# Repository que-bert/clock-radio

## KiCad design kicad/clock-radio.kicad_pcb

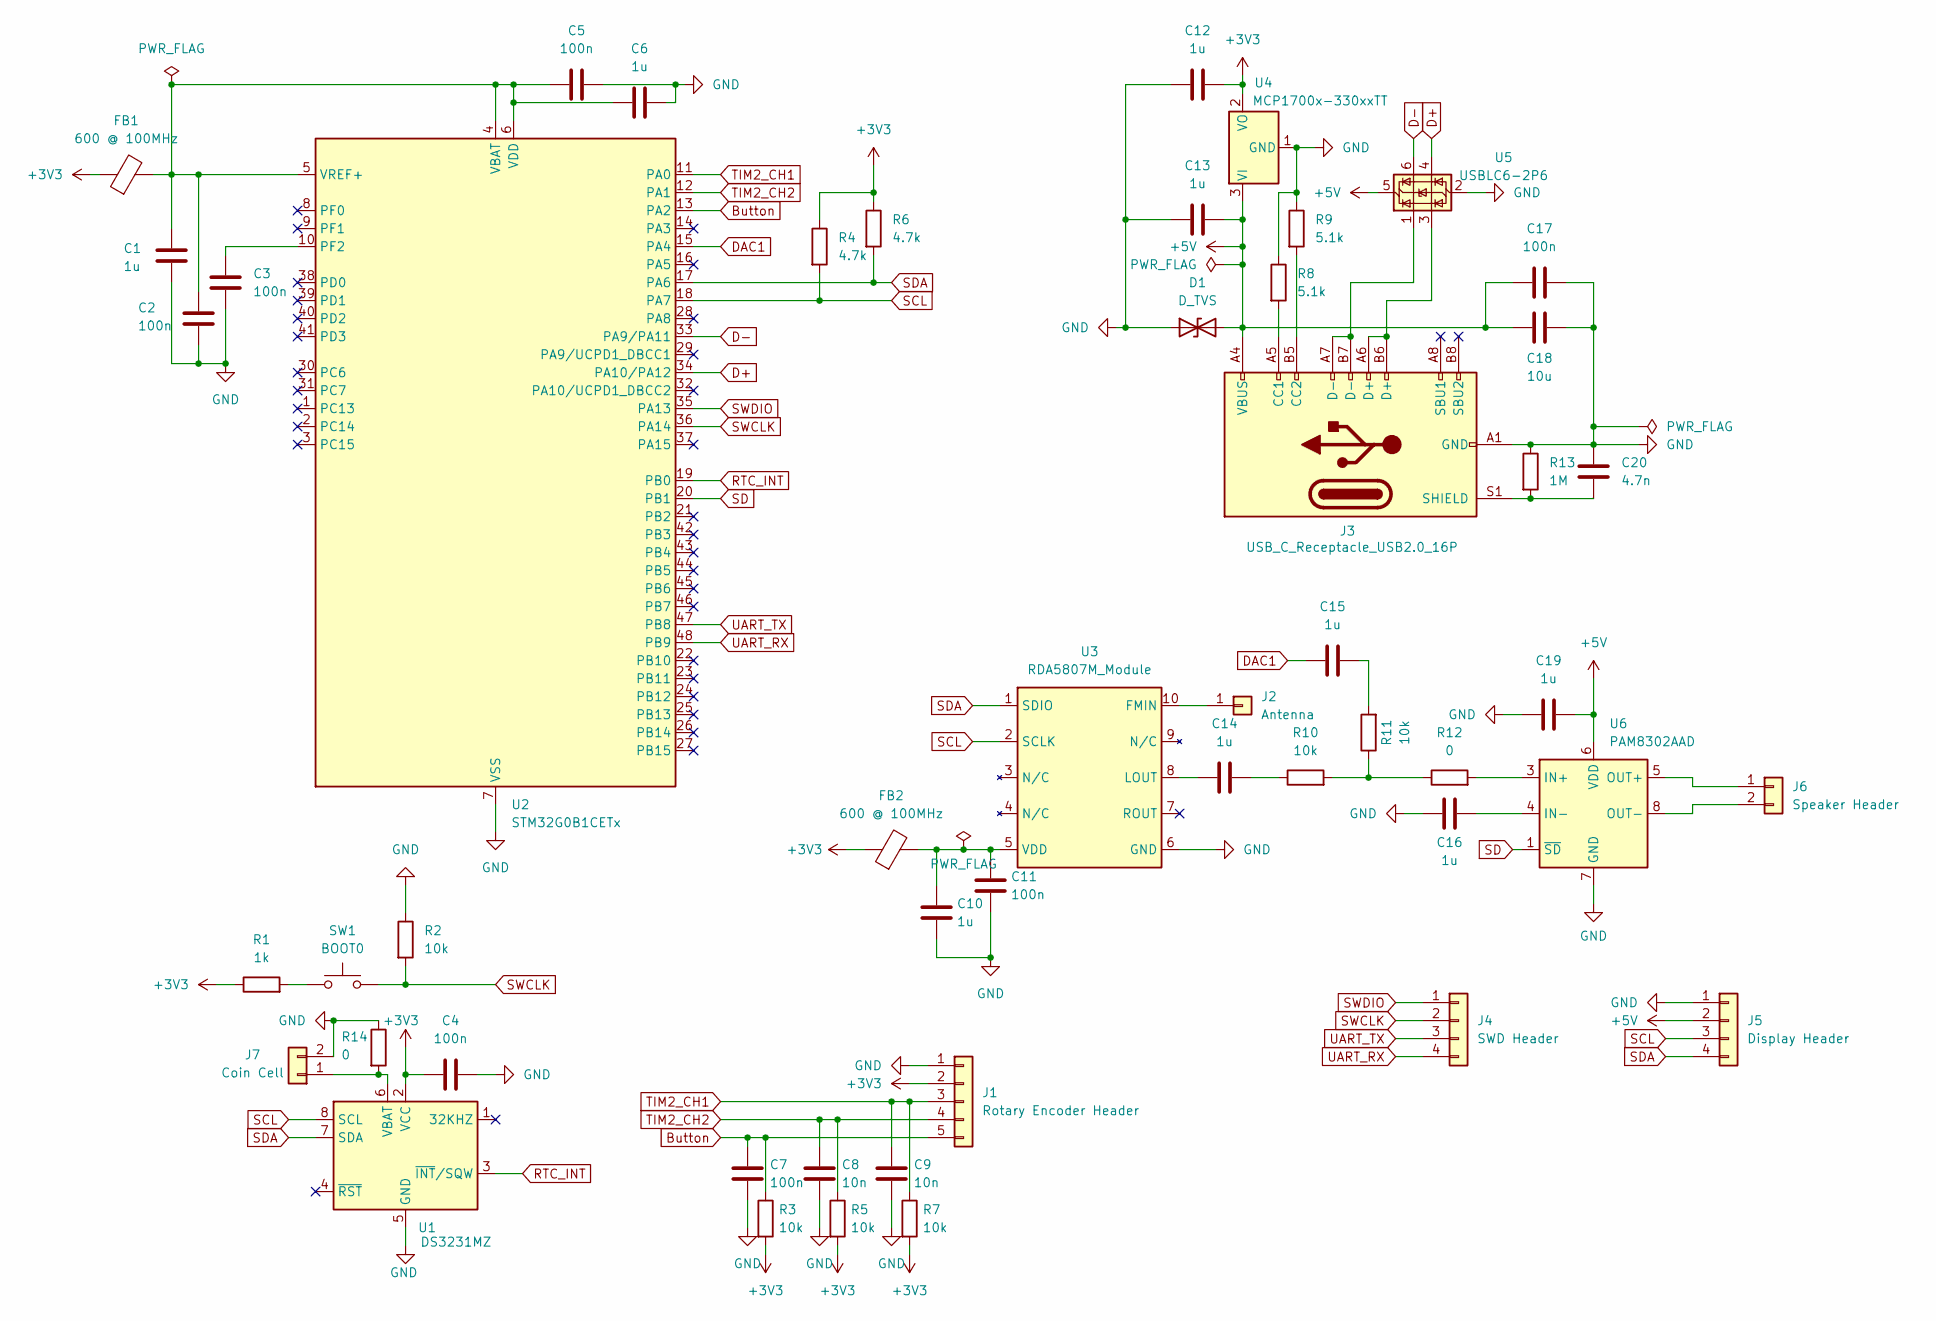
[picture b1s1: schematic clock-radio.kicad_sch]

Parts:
C1, C6, C10, C12, C13, C14, C15, C16, C19: 1u; C_0402_1005Metric_Pad0.74x0.62mm_HandSolder
C2, C3, C4, C5, C7, C11, C17: 100n; C_0402_1005Metric_Pad0.74x0.62mm_HandSolder
C8, C9: 10n; C_0402_1005Metric_Pad0.74x0.62mm_HandSolder
C18: 10u; C_0402_1005Metric_Pad0.74x0.62mm_HandSolder
C20: 4.7n; C_0402_1005Metric_Pad0.74x0.62mm_HandSolder
D1: D_TVS; D_SMA-SMB_Universal_Handsoldering
FB1, FB2: 600 @ 100MHz; C_0603_1608Metric_Pad1.08x0.95mm_HandSolder
J1: Rotary Encoder Header; PinSocket_1x05_P2.54mm_Vertical
J2: Antenna; SolderWire-0.75sqmm_1x01_D1.25mm_OD2.3mm
J3: USB_C_Receptacle_USB2.0_16P; USB_C_Receptacle_HCTL_HC-TYPE-C-16P-01A
J4: SWD Header; PinSocket_1x04_P2.54mm_Vertical
J5: Display Header; PinSocket_1x04_P2.54mm_Vertical
J6: Speaker Header; PinSocket_1x02_P2.54mm_Vertical
J7: Coin Cell; PinSocket_1x02_P2.54mm_Vertical
R1: 1k; R_0402_1005Metric_Pad0.72x0.64mm_HandSolder
R2, R3, R5, R7, R10, R11: 10k; R_0402_1005Metric_Pad0.72x0.64mm_HandSolder
R4, R6: 4.7k; R_0402_1005Metric_Pad0.72x0.64mm_HandSolder
R8, R9: 5.1k; R_0402_1005Metric_Pad0.72x0.64mm_HandSolder
R12, R14: 0; R_0402_1005Metric_Pad0.72x0.64mm_HandSolder
R13: 1M; R_0402_1005Metric_Pad0.72x0.64mm_HandSolder
SW1: BOOT0; SW_SPST_B3U-1000P
U1: DS3231MZ; SOIC-8_3.9x4.9mm_P1.27mm
U2: STM32G0B1CETx; LQFP-48_7x7mm_P0.5mm
U3: RDA5807M_Module; RDA5807M_Module_SM
U4: MCP1700x-330xxTT; SOT-23
U5: USBLC6-2P6; SOT-666
U6: PAM8302AAD; MSOP-8_3x3mm_P0.65mm

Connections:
+3V3: C4.1, C12.2, FB1.1, FB2.1, J1.2, R1.1, R3.2, R4.1, R5.2, R6.1, R7.2, U1.2 (VCC), U4.2 (VO); also elsewhere on the board
+5V: C13.2, C17.1, C18.1, C19.2, D1.2 (A2), J3.A4 (VBUS), J3.A9 (VBUS), J3.B4 (VBUS), J3.B9 (VBUS), J5.2, U4.3 (VI), U5.5 (VBUS), U6.6 (VDD)
Button: C7.1, J1.5, R3.1, U2.13 (PA2)
D+: U2.34 (PA10/PA12), U5.4 (I/O2)
D-: U2.33 (PA9/PA11), U5.6 (I/O1)
DAC1: C15.1, U2.15 (PA4)
GND: C1.1, C2.1, C3.1, C4.2, C5.2, C6.2, C7.2, C8.2, C9.2, C10.2, C11.2, C12.1, C13.1, C16.2, C17.2, C18.2, C19.1, C20.1, D1.1 (A1), J1.1, J3.A1 (GND), J3.A12 (GND), J3.B1 (GND), J3.B12 (GND), J5.1, J7.2, R2.1, R8.1, R9.1, R13.1, R14.1, U1.5 (GND), U2.7 (VSS), U3.6 (GND), U4.1 (GND), U5.2 (GND), U6.7 (GND); also elsewhere on the board
unnamed: C14.2, R10.1
unnamed: C15.2, R11.2
unnamed: J2.1, U3.10 (FMIN)
unnamed: J3.A5 (CC1), R8.2
unnamed: J3.B5 (CC2), R9.2
unnamed: J3.A6 (D+), J3.B6 (D+), U5.3 (I/O2)
unnamed: J3.A7 (D-), J3.B7 (D-), U5.1 (I/O1)
unnamed: C20.2, J3.S1 (SHIELD), R13.2
unnamed: J6.1, U6.5 (OUT+)
unnamed: J6.2, U6.8 (OUT-)
unnamed: J7.1, R14.2, U1.6 (VBAT)
unnamed: R1.2, SW1.1
unnamed: R10.2, R11.1, R12.1
unnamed: C3.2, U2.10 (PF2)
unnamed: C1.2, C2.2, C5.1, C6.1, FB1.2, U2.4 (VBAT), U2.5 (VREF+), U2.6 (VDD)
unnamed: C14.1, U3.8 (LOUT)
unnamed: C10.1, C11.1, FB2.2, U3.5 (VDD)
unnamed: R12.2, U6.3 (IN+)
unnamed: C16.1, U6.4 (IN-)
RTC_INT: U1.3 (~INT/SQW), U2.19 (PB0)
SCL: J5.3, R4.2, U1.8 (SCL), U2.18 (PA7), U3.2 (SCLK)
SD: U2.20 (PB1), U6.1 (~SD)
SDA: J5.4, R6.2, U1.7 (SDA), U2.17 (PA6), U3.1 (SDIO)
SWCLK: J4.2, R2.2, SW1.2, U2.36 (PA14)
SWDIO: J4.1, U2.35 (PA13)
TIM2_CH1: C9.1, J1.3, R7.1, U2.11 (PA0)
TIM2_CH2: C8.1, J1.4, R5.1, U2.12 (PA1)
UART_RX: J4.4, U2.48 (PB9)
UART_TX: J4.3, U2.47 (PB8)

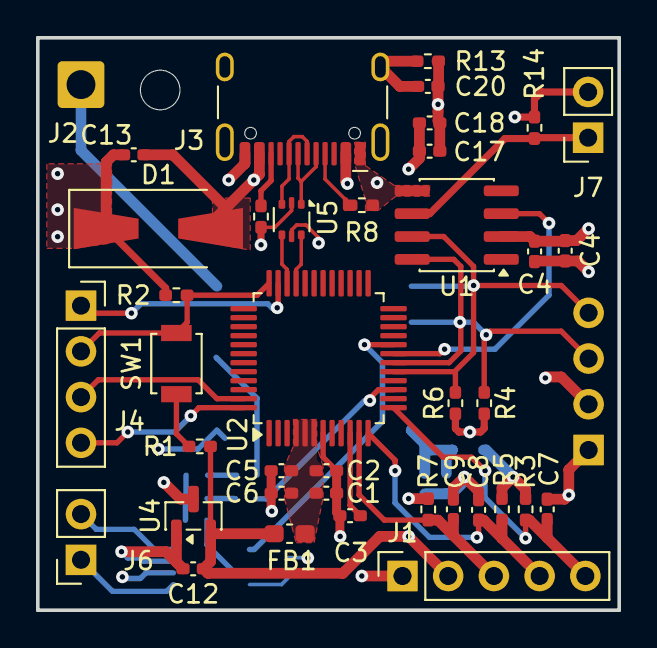
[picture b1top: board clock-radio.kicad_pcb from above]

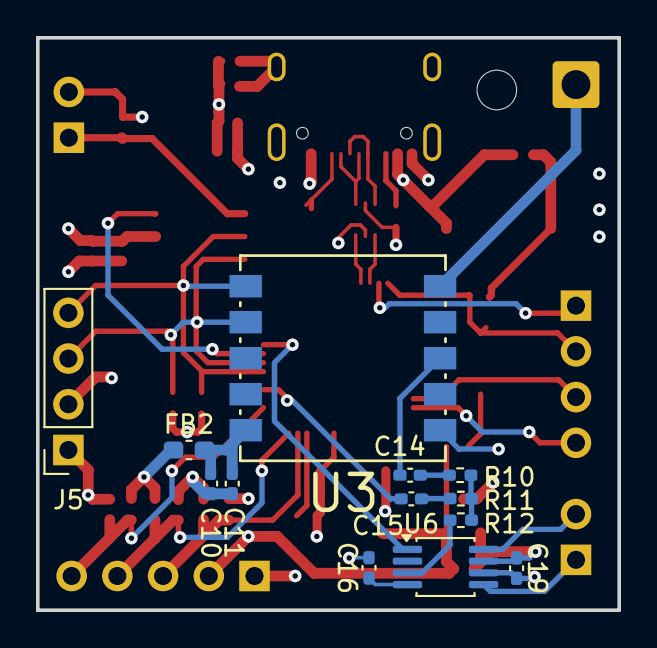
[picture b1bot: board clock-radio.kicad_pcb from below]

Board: 4 copper layers, 32.3 x 31.8 mm, 52 parts (13 on the bottom side), 36 nets.

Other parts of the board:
C4#2: 100n; C_0402_1005Metric_Pad0.74x0.62mm_HandSolder

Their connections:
+3V3: C4#2.2; also elsewhere on the board
GND: C4#2.1; also elsewhere on the board

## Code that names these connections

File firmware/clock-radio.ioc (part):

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Mcu.Name=STM32G0B1C(B-C-E)Tx
Mcu.Package=LQFP48
Mcu.UserName=STM32G0B1CETx
PA0.Signal=S_TIM2_CH1_ETR
PA1.Signal=S_TIM2_CH2
PA11\ [PA9].Mode=Device
PA11\ [PA9].Signal=USB_DM
PA12\ [PA10].Mode=Device
PA12\ [PA10].Signal=USB_DP
PA13.Mode=Serial_Wire
PA13.Signal=SYS_SWDIO
PA14-BOOT0.Mode=Serial_Wire
PA14-BOOT0.Signal=SYS_SWCLK
PA2.GPIOParameters=GPIO_PuPd,GPIO_Label
PA2.GPIO_Label=ENC_BUTTON
PA2.GPIO_PuPd=GPIO_PULLUP
PA2.Signal=GPIO_Input
PA4.Signal=COMP_DAC11_group
PA6.Mode=I2C
PA6.Signal=I2C2_SDA
PA7.Mode=I2C
PA7.Signal=I2C2_SCL
PB0.GPIOParameters=GPIO_PuPd,GPIO_Label,GPIO_ModeDefaultEXTI
PB0.GPIO_Label=RTC_INT
PB0.GPIO_ModeDefaultEXTI=GPIO_MODE_IT_FALLING
PB0.GPIO_PuPd=GPIO_PULLUP
PB0.Signal=GPXTI0
PB1.GPIOParameters=GPIO_Label
PB1.GPIO_Label=AMP_SD
PB1.Signal=GPIO_Output
PB8.Mode=Asynchronous
PB8.Signal=USART3_TX
PB9.Mode=Asynchronous
PB9.Signal=USART3_RX
RCC.HSE_VALUE=8000000
RCC.SYSCLKFreq_VALUE=16000000
board=custom

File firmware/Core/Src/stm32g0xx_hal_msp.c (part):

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
    __HAL_RCC_GPIOA_CLK_ENABLE();
    /**DAC1 GPIO Configuration
    PA4     ------> DAC1_OUT1
    */
    GPIO_InitStruct.Pin = GPIO_PIN_4;
    GPIO_InitStruct.Mode = GPIO_MODE_ANALOG;
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    __HAL_RCC_DAC1_CLK_DISABLE();

    /**DAC1 GPIO Configuration
    PA4     ------> DAC1_OUT1
    */
    HAL_GPIO_DeInit(GPIOA, GPIO_PIN_4);

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
    __HAL_RCC_GPIOA_CLK_ENABLE();
    /**I2C2 GPIO Configuration
    PA6     ------> I2C2_SDA
    PA7     ------> I2C2_SCL
    */
    GPIO_InitStruct.Pin = GPIO_PIN_6|GPIO_PIN_7;
    GPIO_InitStruct.Mode = GPIO_MODE_AF_OD;
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    __HAL_RCC_I2C2_CLK_DISABLE();

    /**I2C2 GPIO Configuration
    PA6     ------> I2C2_SDA
    PA7     ------> I2C2_SCL
    */
    HAL_GPIO_DeInit(GPIOA, GPIO_PIN_6);

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
    __HAL_RCC_GPIOA_CLK_ENABLE();
    /**TIM2 GPIO Configuration
    PA0     ------> TIM2_CH1
    PA1     ------> TIM2_CH2
    */
    GPIO_InitStruct.Pin = GPIO_PIN_0|GPIO_PIN_1;
    GPIO_InitStruct.Mode = GPIO_MODE_AF_PP;
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    __HAL_RCC_TIM2_CLK_DISABLE();

    /**TIM2 GPIO Configuration
    PA0     ------> TIM2_CH1
    PA1     ------> TIM2_CH2
    */
    HAL_GPIO_DeInit(GPIOA, GPIO_PIN_0|GPIO_PIN_1);

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
    __HAL_RCC_GPIOB_CLK_ENABLE();
    /**USART3 GPIO Configuration
    PB8     ------> USART3_TX
    PB9     ------> USART3_RX
    */
    GPIO_InitStruct.Pin = GPIO_PIN_8|GPIO_PIN_9;
    GPIO_InitStruct.Mode = GPIO_MODE_AF_PP;
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    __HAL_RCC_USART3_CLK_DISABLE();

    /**USART3 GPIO Configuration
    PB8     ------> USART3_TX
    PB9     ------> USART3_RX
    */
    HAL_GPIO_DeInit(GPIOB, GPIO_PIN_8|GPIO_PIN_9);

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
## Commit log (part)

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2026-06-11 Added decoupling capacitors and ferrite bead on radio module
2026-06-11 started pcb design
2026-06-15 updated pcb layout
2026-06-17 added coin cell
2026-06-20 connected all components and added in ground and power plane
2026-06-20 Check out antenna footprint
2026-06-20 swapped layers
2026-06-20 deleted duplicate project files
2026-06-20 Added m2 hole
2026-06-20 Added gerber files
2026-06-23 updated cap

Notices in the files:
firmware/Core/Src/stm32g0xx_hal_msp.c:
Copyright (c) 2026 STMicroelectronics.
All rights reserved.
This software is licensed under terms that can be found in the LICENSE file
